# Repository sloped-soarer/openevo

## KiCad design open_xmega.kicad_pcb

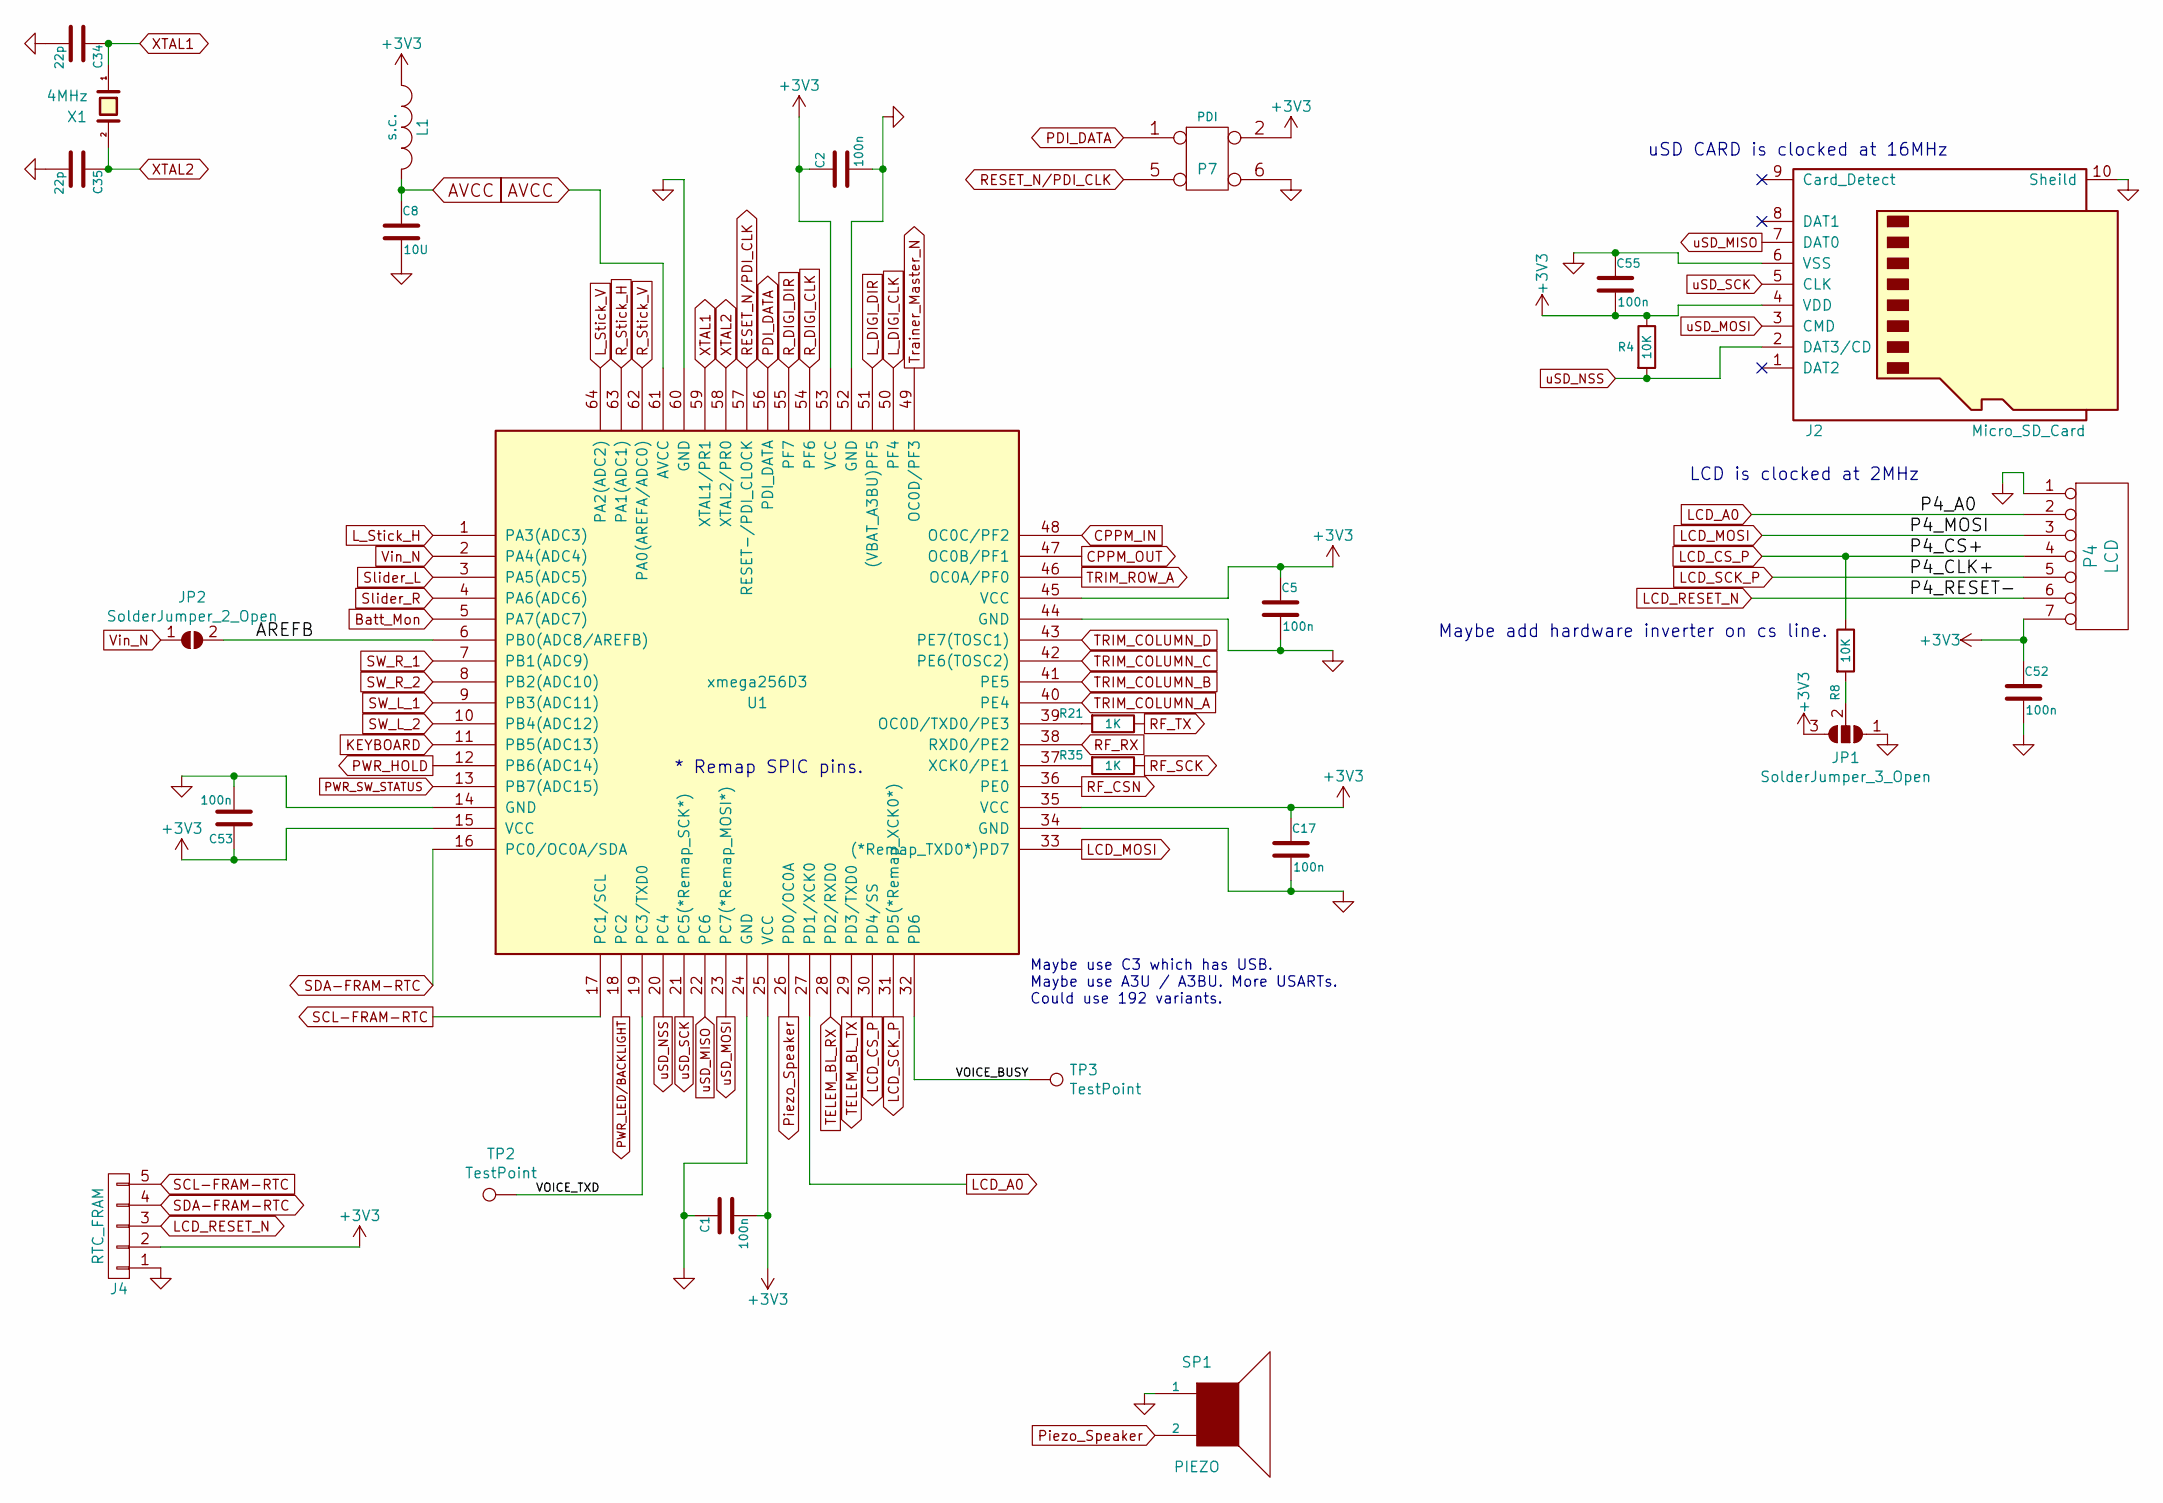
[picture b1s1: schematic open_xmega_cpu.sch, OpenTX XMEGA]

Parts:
C1, C2, C5, C17, C52, C53, C55: 100n; SM0805
C8: 10U; SM1206POL
C34, C35: 22p; SM0805
J2: Micro_SD_Card; HRS_uSD_DM3CS
J4: RTC_FRAM; AVX_00-9159005551X06
JP1: SolderJumper_3_Open; SolderJumper-3_P1.3mm_Open_RoundedPad1.0x1.5mm
JP2: SolderJumper_2_Open; SolderJumper-2_P1.3mm_Open_RoundedPad1.0x1.5mm
L1: s.c.; SM0805
P4: LCD; MOLEX_52808-0770
P7: PDI; PinHeader_2x03_P2.54mm_Vertical_missing_3&4
R4, R8: 10K; SM0805
R21, R35: 1K; SM0805
SP1: PIEZO; Sounder_ABT-436-RC
TP2, TP3: TestPoint; TestPoint_THTPad_1.0x1.0mm_Drill0.5mm
U1: xmega256D3; TQFP64
X1: 4MHz; Crystal_SMD_HC49-SD

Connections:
+3V3: C1.2, C2.1, C5.1, C17.1, C52.1, C53.1, C55.2, J2.4 (VDD), J4.2, JP1.3 (B), L1.1, P4.7, P7.2, R4.1, U1.15 (VCC), U1.25 (VCC), U1.35 (VCC), U1.45 (VCC), U1.53 (VCC); also elsewhere on the board
/open_xmega_cpu/AREFB: JP2.2 (B), U1.6 (PB0(ADC8/AREFB))
/open_xmega_cpu/VOICE_BUSY: TP3.1, U1.32 (PD6)
/open_xmega_cpu/VOICE_TXD: TP2.1, U1.19 (PC3/TXD0)
AVCC: C8.1, L1.2, U1.61 (AVCC)
Batt_Mon: U1.5 (PA7(ADC7)); also elsewhere on the board
CPPM_IN: U1.48 (OC0C/PF2); also elsewhere on the board
CPPM_OUT: U1.47 (OC0B/PF1); also elsewhere on the board
GND: C1.1, C2.2, C5.2, C8.2, C17.2, C34.2, C35.2, C52.2, C53.2, C55.1, J2.6 (VSS), J2.10 (Sheild), J4.1, JP1.1 (A), P4.1, P7.6, SP1.1, U1.14 (GND), U1.24 (GND), U1.34 (GND), U1.44 (GND), U1.52 (GND), U1.60 (GND); also elsewhere on the board
KEYBOARD: U1.11 (PB5(ADC13)); also elsewhere on the board
LCD_A0: P4.2, U1.27 (PD1/XCK0)
LCD_CS_P: P4.4, R8.1, U1.30 (PD4/SS)
LCD_MOSI: P4.3, U1.33 ((*Remap_TXD0*)PD7)
LCD_RESET_N: J4.3, P4.6
LCD_SCK_P: P4.5, U1.31 (PD5(*Remap_XCK0*))
L_DIGI_CLK: U1.50 (PF4); also elsewhere on the board
L_DIGI_DIR: U1.51 ((VBAT_A3BU)PF5); also elsewhere on the board
L_Stick_H: U1.1 (PA3(ADC3)); also elsewhere on the board
L_Stick_V: U1.64 (PA2(ADC2)); also elsewhere on the board
unnamed: JP1.2 (C), R8.2
unnamed: R21.2, U1.39 (OC0D/TXD0/PE3)
unnamed: R35.2, U1.37 (XCK0/PE1)
PDI_DATA: P7.1, U1.56 (PDI_DATA)
PWR_HOLD: U1.12 (PB6(ADC14)); also elsewhere on the board
PWR_LED/BACKLIGHT: U1.18 (PC2); also elsewhere on the board
PWR_SW_STATUS: U1.13 (PB7(ADC15)); also elsewhere on the board
Piezo_Speaker: SP1.2, U1.26 (PD0/OC0A)
RESET_N/PDI_CLK: P7.5, U1.57 (RESET-/PDI_CLOCK); also elsewhere on the board
RF_CSN: U1.36 (PE0); also elsewhere on the board
RF_RX: U1.38 (RXD0/PE2); also elsewhere on the board
RF_SCK: R35.1; also elsewhere on the board
RF_TX: R21.1; also elsewhere on the board
R_DIGI_CLK: U1.54 (PF6); also elsewhere on the board
R_DIGI_DIR: U1.55 (PF7); also elsewhere on the board
R_Stick_H: U1.63 (PA1(ADC1)); also elsewhere on the board
R_Stick_V: U1.62 (PA0(AREFA/ADC0)); also elsewhere on the board
SCL-FRAM-RTC: J4.5, U1.17 (PC1/SCL)
SDA-FRAM-RTC: J4.4, U1.16 (PC0/OC0A/SDA)
SW_L_1: U1.9 (PB3(ADC11)); also elsewhere on the board
SW_L_2: U1.10 (PB4(ADC12)); also elsewhere on the board
SW_R_1: U1.7 (PB1(ADC9)); also elsewhere on the board
SW_R_2: U1.8 (PB2(ADC10)); also elsewhere on the board
Slider_L: U1.3 (PA5(ADC5)); also elsewhere on the board
Slider_R: U1.4 (PA6(ADC6)); also elsewhere on the board
TELEM_BL_RX: U1.28 (PD2/RXD0); also elsewhere on the board
TELEM_BL_TX: U1.29 (PD3/TXD0); also elsewhere on the board
TRIM_COLUMN_A: U1.40 (PE4); also elsewhere on the board
TRIM_COLUMN_B: U1.41 (PE5); also elsewhere on the board
TRIM_COLUMN_C: U1.42 (PE6(TOSC2)); also elsewhere on the board
TRIM_COLUMN_D: U1.43 (PE7(TOSC1)); also elsewhere on the board
TRIM_ROW_A: U1.46 (OC0A/PF0); also elsewhere on the board
Trainer_Master_N: U1.49 (OC0D/PF3); also elsewhere on the board
Vin_N: JP2.1 (A), U1.2 (PA4(ADC4)); also elsewhere on the board
XTAL1: C34.1, U1.59 (XTAL1/PR1), X1.1 (a)
XTAL2: C35.1, U1.58 (XTAL2/PR0), X1.2 (b)
uSD_MISO: J2.7 (DAT0), U1.22 (PC6)
uSD_MOSI: J2.3 (CMD), U1.23 (PC7(*Remap_MOSI*))
uSD_NSS: J2.2 (DAT3/CD), R4.2, U1.20 (PC4)
uSD_SCK: J2.5 (CLK), U1.21 (PC5(*Remap_SCK*))

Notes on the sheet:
LCD is clocked at 2MHz
* Remap SPIC pins.
uSD CARD is clocked at 16MHz
Maybe use C3 which has USB. Maybe use A3U / A3BU. More USARTs. Could use 192 variants.
Maybe add hardware inverter on cs line.

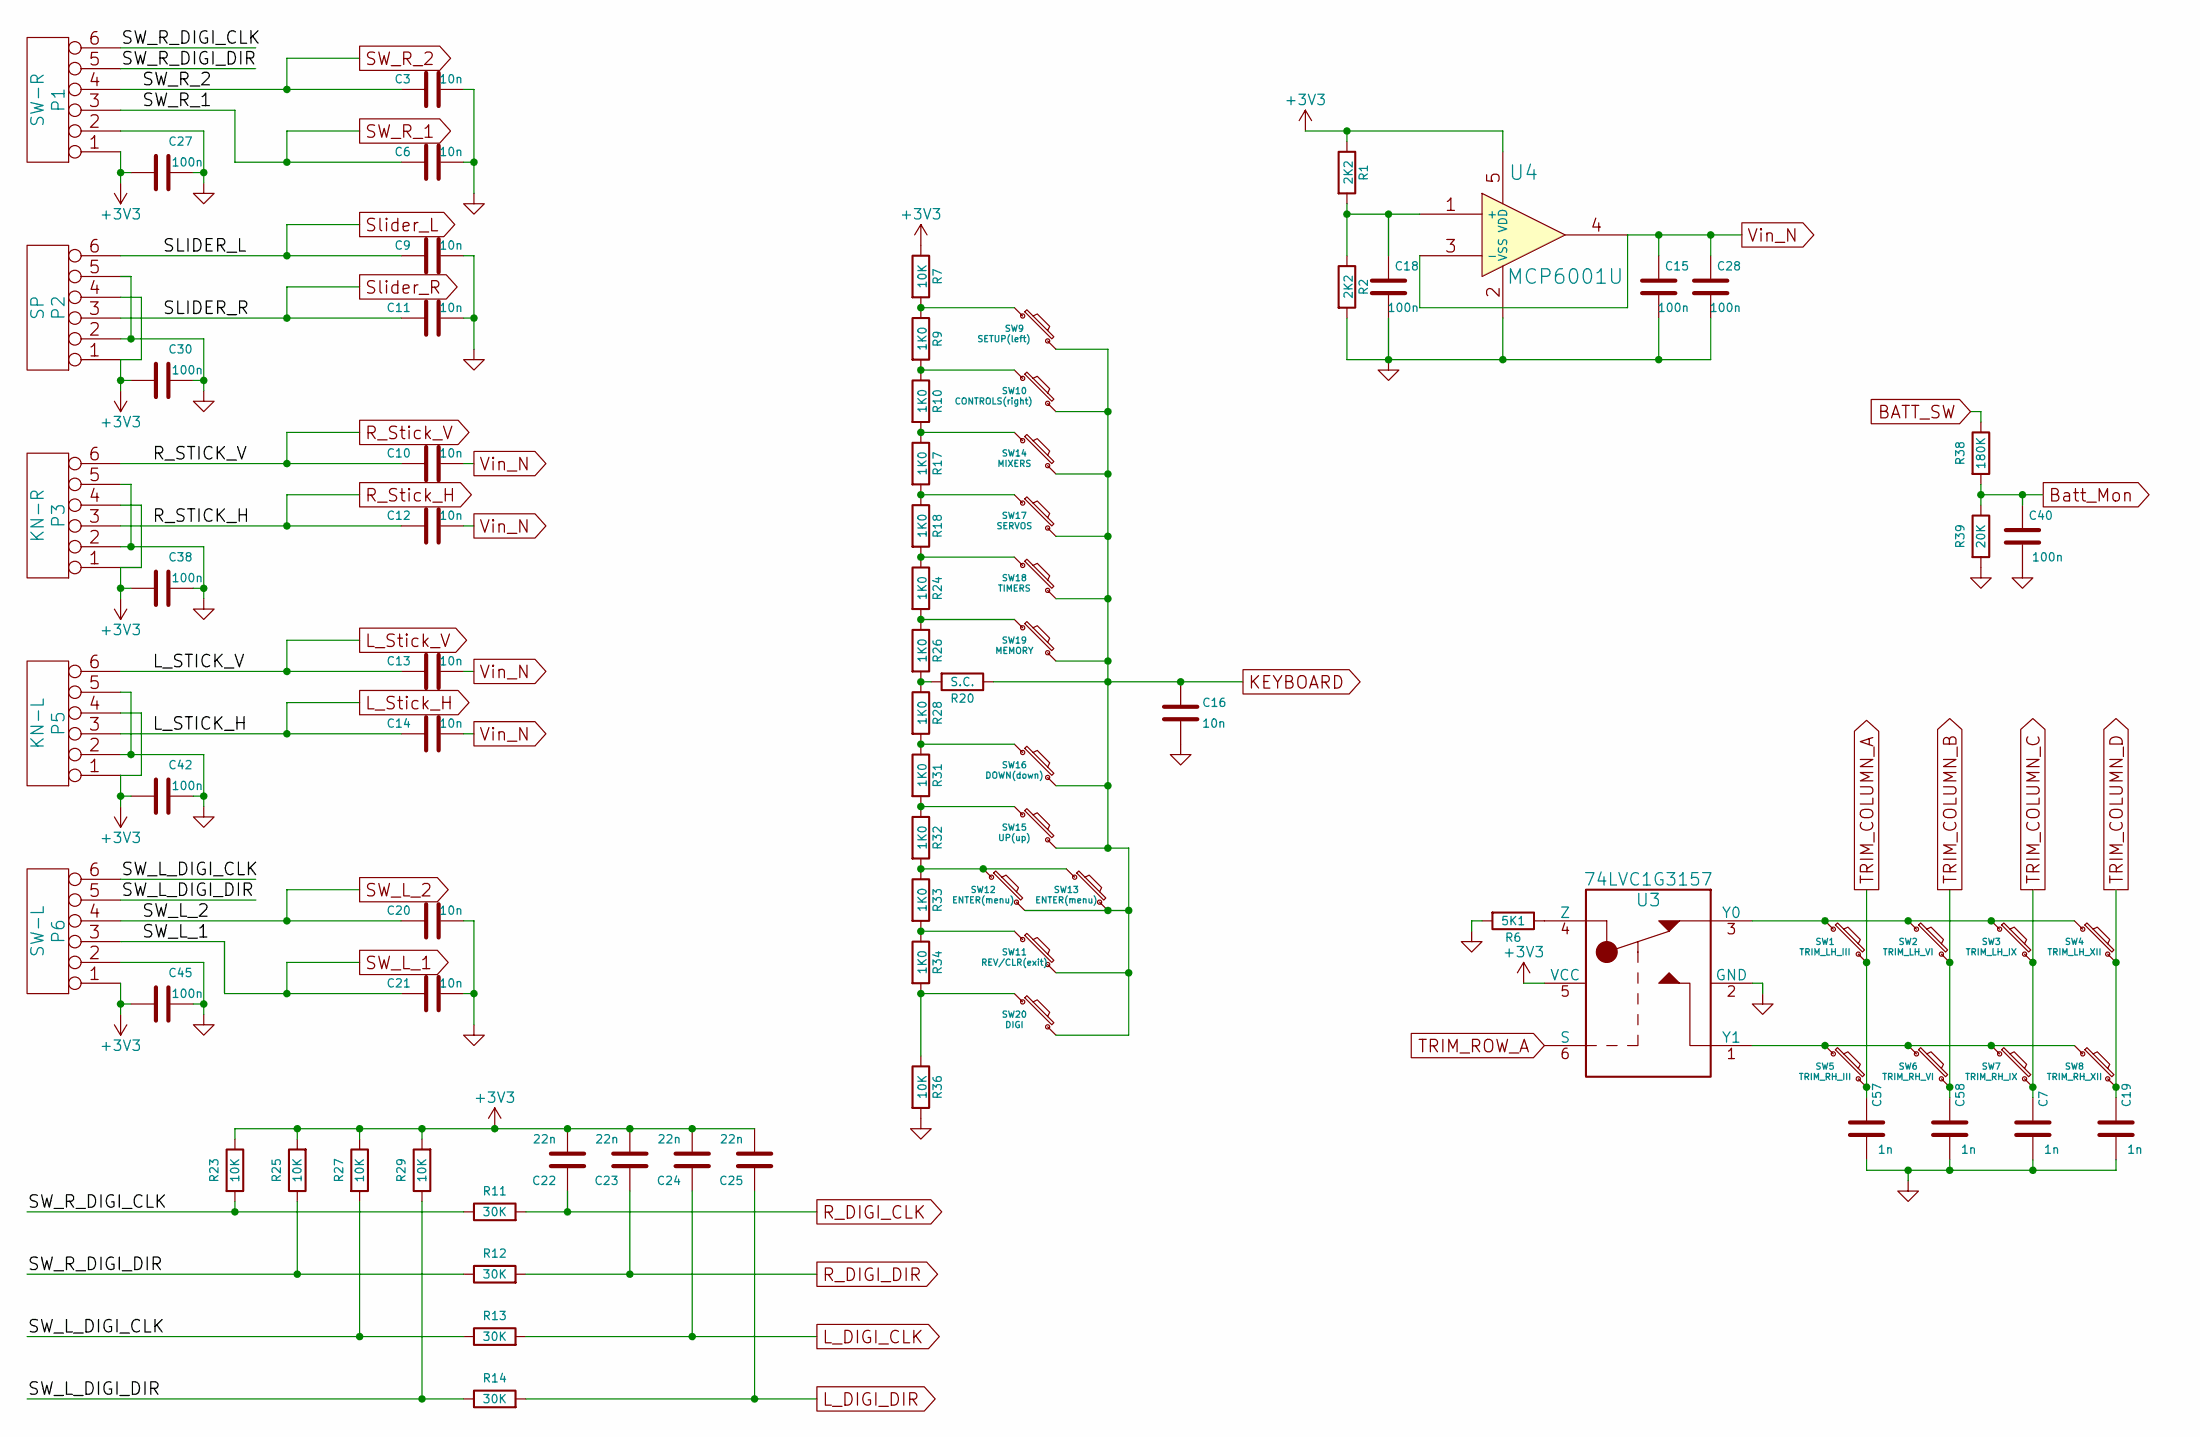
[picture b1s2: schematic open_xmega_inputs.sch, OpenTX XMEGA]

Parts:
C3, C6, C9, C10, C11, C12, C13, C14, C16, C20, C21: 10n; SM0805
C7, C19, C57, C58: 1n; SM0805
C15, C18, C27, C28, C30, C38, C40, C42, C45: 100n; SM0805
C22, C23, C24, C25: 22n; SM0805
P1: SW-R; JST_B6B-ZR-3.4
P2: SP; JST_B6B-ZR-3.4
P3: KN-R; JST_B6B-ZR-3.4
P5: KN-L; JST_B6B-ZR-3.4
P6: SW-L; JST_B6B-ZR-3.4
R1, R2: 2K2; SM0805
R6: 5K1; SM0805
R7, R23, R25, R27, R29, R36: 10K; SM0805
R9, R10, R17, R18, R24, R26, R28, R31, R32, R33, R34: 1K0; SM0805
R11, R12, R13, R14: 30K; SM0805
R20: S.C.; SM0805
R38: 180K; SM0805
R39: 20K; SM0805
SW1: TRIM_LH_III; sw_tact_6x6_smd
SW2: TRIM_LH_VI; sw_tact_6x6_smd
SW3: TRIM_LH_IX; sw_tact_6x6_smd
SW4: TRIM_LH_XII; sw_tact_6x6_smd
SW5: TRIM_RH_III; sw_tact_6x6_smd
SW6: TRIM_RH_VI; sw_tact_6x6_smd
SW7: TRIM_RH_IX; sw_tact_6x6_smd
SW8: TRIM_RH_XII; sw_tact_6x6_smd
SW9: SETUP(left); sw_tact_6x6_smd
SW10: CONTROLS(right); sw_tact_6x6_smd
SW11: REV/CLR(exit); sw_tact_6x6_smd
SW12, SW13: ENTER(menu); sw_tact_6x6_smd
SW14: MIXERS; sw_tact_6x6_smd
SW15: UP(up); sw_tact_6x6_smd
SW16: DOWN(down); sw_tact_6x6_smd
SW17: SERVOS; sw_tact_6x6_smd
SW18: TIMERS; sw_tact_6x6_smd
SW19: MEMORY; sw_tact_6x6_smd
SW20: DIGI; sw_tact_6x6_smd
U3: 74LVC1G3157; SOT-23-6
U4: MCP6001U; SOT-23-5

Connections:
+3V3: C22.2, C23.2, C24.2, C25.2, C27.1, C30.1, C38.1, C42.1, C45.1, P1.1, P2.1, P2.4, P3.1, P3.4, P5.1, P5.4, P6.1, R1.1, R7.1, R23.1, R25.2, R27.1, R29.2, U3.5 (VCC), U4.5 (VDD); also elsewhere on the board
/open_xmega_inputs/SW_L_DIGI_CLK: P6.6, R13.1, R27.2
/open_xmega_inputs/SW_L_DIGI_DIR: P6.5, R14.1, R29.1
/open_xmega_inputs/SW_R_DIGI_CLK: P1.6, R11.1, R23.2
/open_xmega_inputs/SW_R_DIGI_DIR: P1.5, R12.1, R25.1
BATT_SW: R38.1; also elsewhere on the board
Batt_Mon: C40.2, R38.2, R39.1; also elsewhere on the board
GND: C3.2, C6.2, C7.2, C9.2, C11.2, C15.1, C16.2, C18.1, C19.2, C20.2, C21.2, C27.2, C28.1, C30.2, C38.2, C40.1, C42.2, C45.2, C57.2, C58.2, P1.2, P2.2, P2.5, P3.2, P3.5, P5.2, P5.5, P6.2, R2.2, R6.2, R36.2, R39.2, U3.2 (GND), U4.2 (VSS); also elsewhere on the board
KEYBOARD: C16.1, R20.1, SW9.2, SW10.2, SW11.2, SW12.2, SW13.2, SW14.2, SW15.2, SW16.2, SW17.2, SW18.2, SW19.2, SW20.2; also elsewhere on the board
L_DIGI_CLK: C24.1, R13.2; also elsewhere on the board
L_DIGI_DIR: C25.1, R14.2; also elsewhere on the board
L_Stick_H: C14.1, P5.3; also elsewhere on the board
L_Stick_V: C13.1, P5.6; also elsewhere on the board
unnamed: C18.2, R1.2, R2.1, U4.1 (+)
unnamed: R6.1, U3.4 (Z)
unnamed: R7.2, R9.1, SW9.1
unnamed: R9.2, R10.1, SW10.1
unnamed: R10.2, R17.1, SW14.1
unnamed: R17.2, R18.1, SW17.1
unnamed: R18.2, R24.1, SW18.1
unnamed: R20.2, R26.2, R28.1
unnamed: R24.2, R26.1, SW19.1
unnamed: R28.2, R31.1, SW16.1
unnamed: R31.2, R32.1, SW15.1
unnamed: R32.2, R33.1, SW12.1, SW13.1
unnamed: R33.2, R34.1, SW11.1
unnamed: R34.2, R36.1, SW20.1
unnamed: SW1.1, SW2.1, SW3.1, SW4.1, U3.3 (Y0)
unnamed: SW5.1, SW6.1, SW7.1, SW8.1, U3.1 (Y1)
R_DIGI_CLK: C22.1, R11.2; also elsewhere on the board
R_DIGI_DIR: C23.1, R12.2; also elsewhere on the board
R_Stick_H: C12.1, P3.3; also elsewhere on the board
R_Stick_V: C10.1, P3.6; also elsewhere on the board
SW_L_1: C21.1, P6.3; also elsewhere on the board
SW_L_2: C20.1, P6.4; also elsewhere on the board
SW_R_1: C6.1, P1.3; also elsewhere on the board
SW_R_2: C3.1, P1.4; also elsewhere on the board
Slider_L: C9.1, P2.6; also elsewhere on the board
Slider_R: C11.1, P2.3; also elsewhere on the board
TRIM_COLUMN_A: C57.1, SW1.2, SW5.2; also elsewhere on the board
TRIM_COLUMN_B: C58.1, SW2.2, SW6.2; also elsewhere on the board
TRIM_COLUMN_C: C7.1, SW3.2, SW7.2; also elsewhere on the board
TRIM_COLUMN_D: C19.1, SW4.2, SW8.2; also elsewhere on the board
TRIM_ROW_A: U3.6 (S); also elsewhere on the board
Vin_N: C10.2, C12.2, C13.2, C14.2, C15.2, C28.2, U4.3 (-), U4.4; also elsewhere on the board

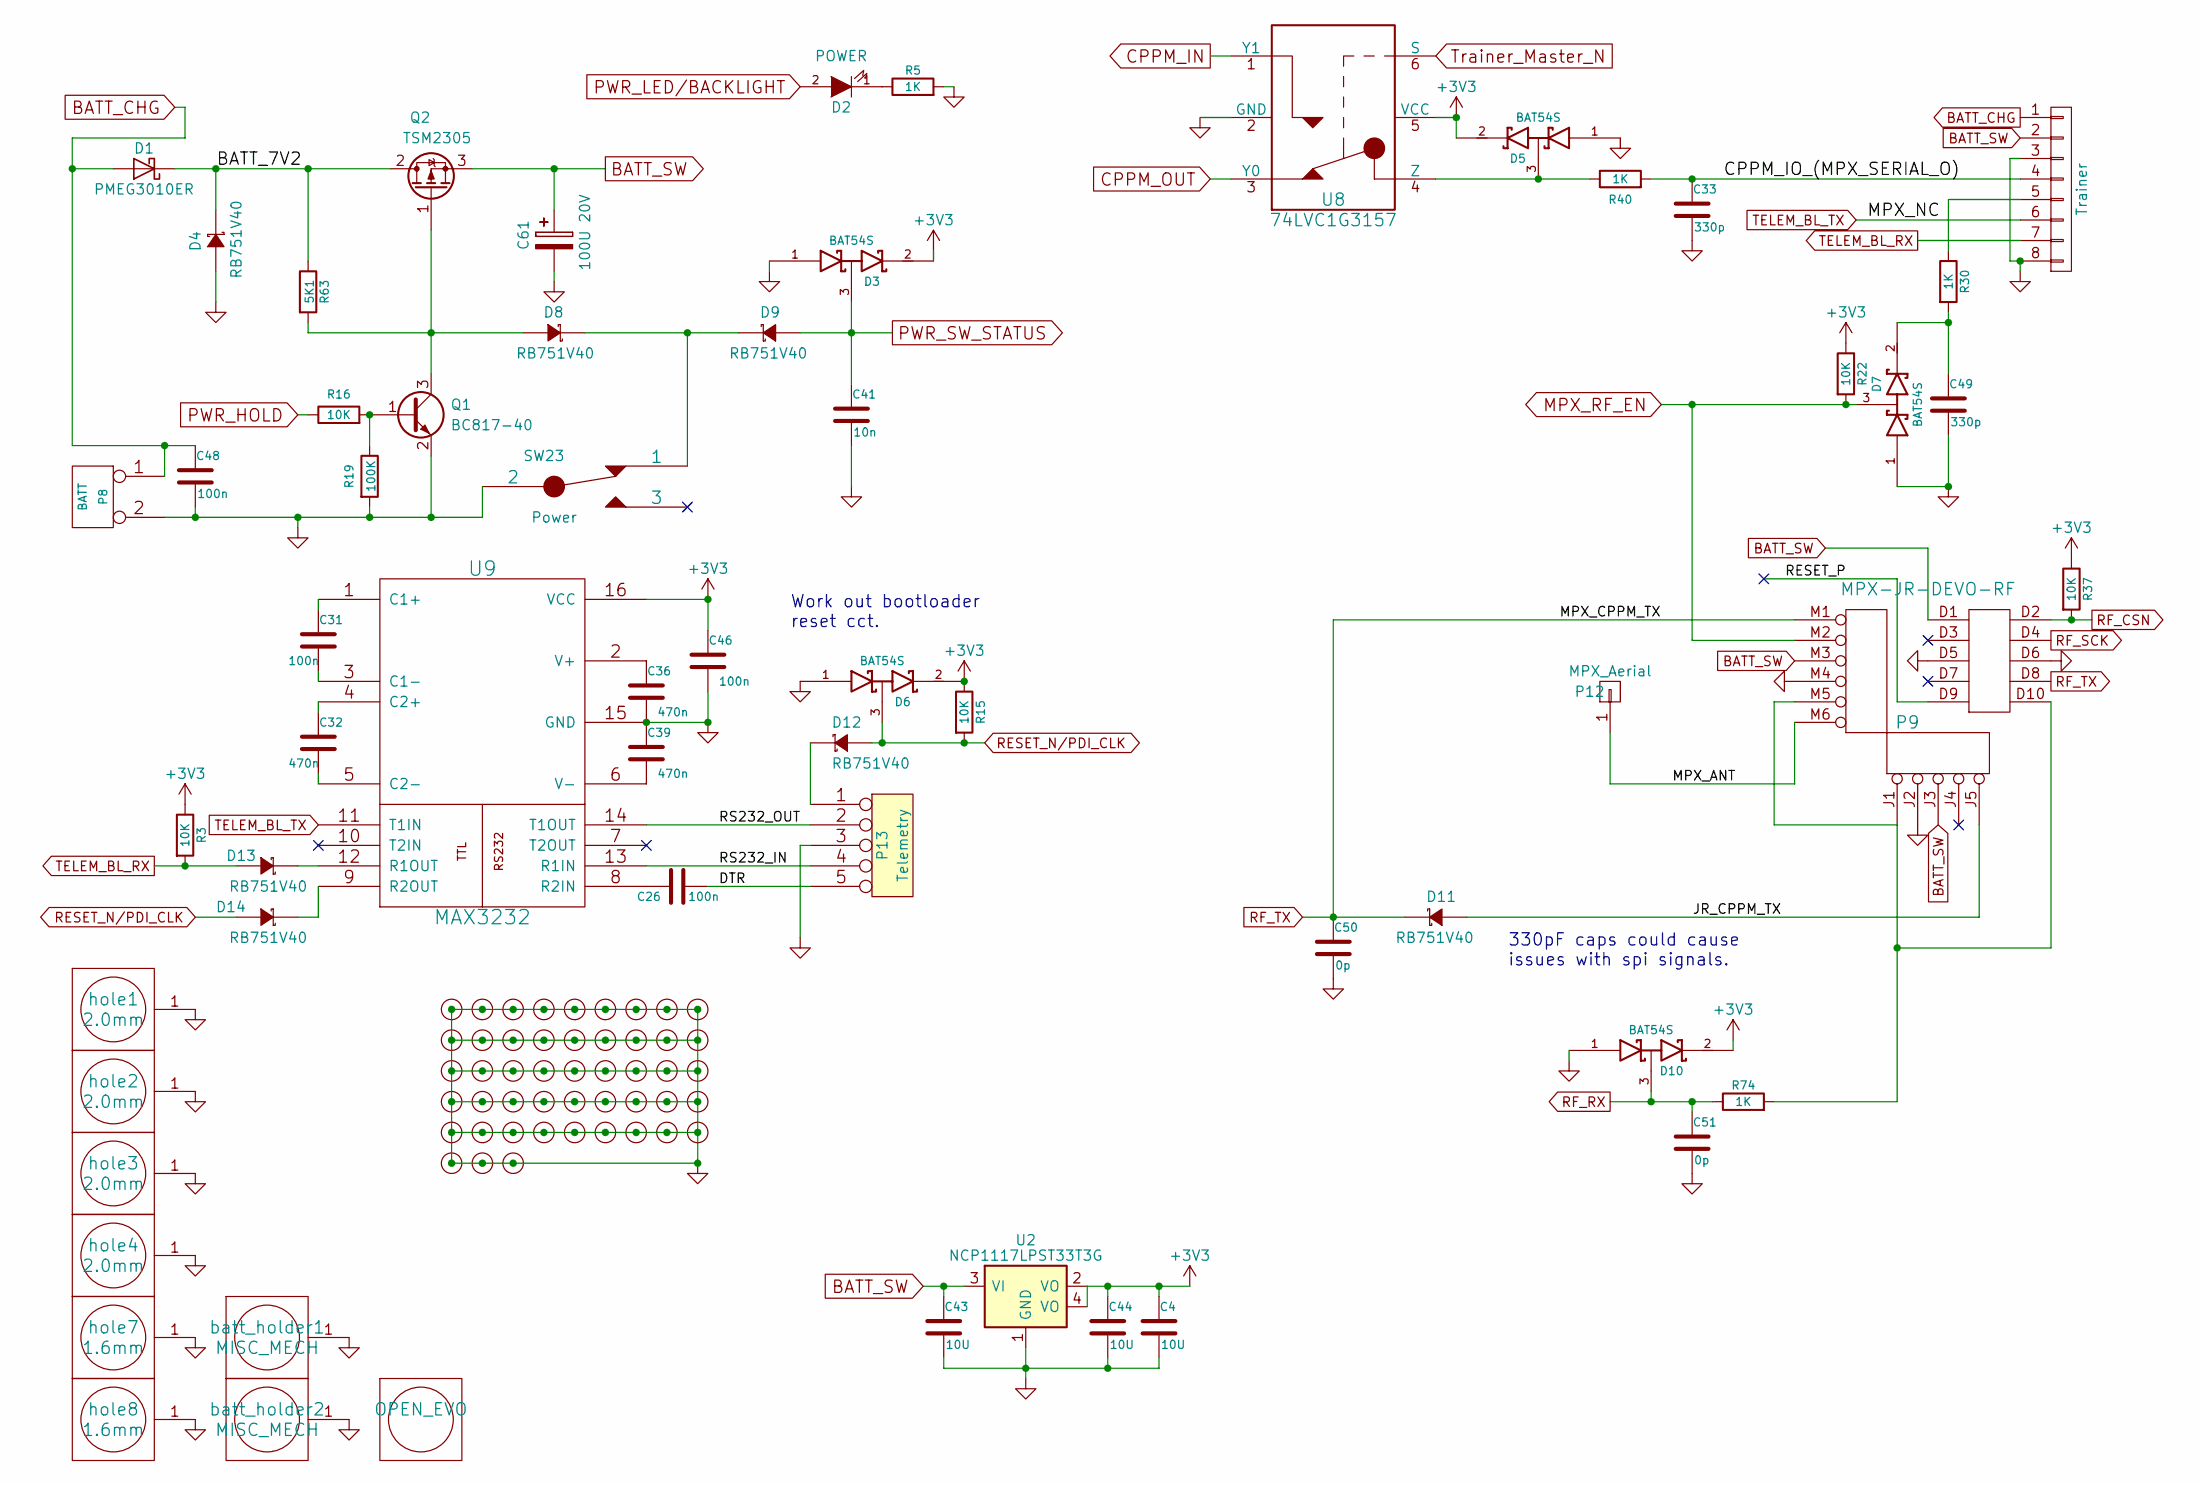
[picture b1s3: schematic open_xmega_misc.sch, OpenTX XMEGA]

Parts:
C4, C43, C44: 10U; SM1206POL
C26, C31, C46, C48: 100n; SM0805
C32, C36, C39: 470n; SM0805
C33, C49: 330p; SM0805
C41: 10n; SM0805
C50, C51: 0p; SM0805
C61: 100U 20V; CP_Elec_6.3x7.7
D1: PMEG3010ER; SOD-123W
D2: POWER; LED_D5.0mm_FlatTop
D3, D5, D6, D7, D10: BAT54S; SOT-23
D4, D8, D9, D11, D12, D13, D14: RB751V40; SOD-323
Logo1: OPEN_EVO; OPEN_EVO_logo
P8: BATT; Lumberg_732782
P9: MPX-JR-DEVO-RF; RF_MODULE
P10: Trainer; Generic_DIN_7_hirschmann-cui
P12: MPX_Aerial; aerial_tag
P13: Telemetry; PinHeader_1x05_P2.54mm_Vertical
Q1: BC817-40; SOT-23
Q2: TSM2305; SOT-23
R3, R15, R16, R22, R37: 10K; SM0805
R5, R30, R40, R74: 1K; SM0805
R19: 100K; SM0805
R63: 5K1; SM0805
SW23: Power; SW_COMAX6_SPDT
U2: NCP1117LPST33T3G; SOT-223
U8: 74LVC1G3157; SOT-23-6
U9: MAX3232; SOIC-16
batt_holder1, batt_holder2: MISC_MECH; evo_battery_holder
hole1, hole2, hole3, hole4: 2.0mm; hole_2-0mm
hole7, hole8: 1.6mm; hole_1-6mm
v1, v2, v3, v4, v5, v6, v7, v8, v9, v10, v11, v12, v13, v14, v15, v16, v17, v18, v19, v20, v21, v22, v23, v24, v25, v26, v27, v28, v29, v30, v31, v32, v33, v34, v35, v36, v37, v38, v39, v40, v41, v42, v43, v44, v45, v46, v47, v48: gnd_via; GND_PLANE_VIA

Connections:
+3V3: C4.1, C44.1, C46.1, D3.2 (K), D5.2 (K), D6.2 (K), D10.2 (K), R3.1, R15.1, R22.1, R37.1, U2.2 (VO), U2.4 (VO), U8.5 (VCC), U9.16 (VCC); also elsewhere on the board
/open_xmega_misc/BATT_7V2: D1.1 (K), D4.1 (K), Q2.2 (D), R63.1
/open_xmega_misc/CPPM_IO_(MPX_SERIAL_O): C33.1, P10.4, R40.2
/open_xmega_misc/DTR: C26.1, P13.5
/open_xmega_misc/JR_CPPM_TX: D11.2 (A), P9.J5 (JR_CPPM)
/open_xmega_misc/MPX_ANT: P9.M6 (MPX_ANT), P12.1
/open_xmega_misc/RESET_P: P9.D9 (RESET_P)
/open_xmega_misc/RS232_IN: P13.4, U9.13 (R1IN)
/open_xmega_misc/RS232_OUT: P13.2, U9.14 (T1OUT)
BATT_CHG: C48.1, D1.2 (A), P8.1, P10.1
BATT_SW: C43.1, C61.1, P9.D1 (+5V), P9.J3 (JR_PWR), P9.M3 (MPX_PWR), P10.2, Q2.3 (S), U2.3 (VI); also elsewhere on the board
CPPM_IN: U8.1 (Y1); also elsewhere on the board
CPPM_OUT: U8.3 (Y0); also elsewhere on the board
GND: C4.2, C33.2, C36.2, C39.1, C41.2, C43.2, C44.2, C46.2, C48.2, C49.2, C50.2, C51.2, C61.2, D3.1 (A), D4.2 (A), D5.1 (A), D6.1 (A), D7.1 (A), D10.1 (A), P8.2 (PM), P9.D5 (GND), P9.D6 (GND), P9.J2 (JR_GND), P9.M4 (MPX_GND), P10.3, P10.8, P13.3, Q1.2 (E), R5.2, R19.2, SW23.2, U2.1 (GND), U8.2 (GND), U9.15 (GND), batt_holder1.1, batt_holder2.1, hole1.1, hole2.1, hole3.1, hole4.1, hole7.1, hole8.1, v1.1, v2.1, v3.1, v4.1, v5.1, v6.1, v7.1, v8.1, v9.1, v10.1, v11.1, v12.1, v13.1, v14.1, v15.1, v16.1, v17.1, v18.1, v19.1, v20.1, v21.1, v22.1, v23.1, v24.1, v25.1, v26.1, v27.1, v28.1, v29.1, v30.1, v31.1, v32.1, v33.1, v34.1, v35.1, v36.1, v37.1, v38.1, v39.1, v40.1, v41.1, v42.1, v43.1, v44.1, v45.1, v46.1, v47.1, v48.1; also elsewhere on the board
MPX_RF_EN: D7.3 (AK), P9.M2 (MPX_RF_EN), R22.2
unnamed: C26.2, U9.8 (R2IN)
unnamed: C31.1, U9.1 (C1+)
unnamed: C31.2, U9.3 (C1-)
unnamed: C32.1, U9.4 (C2+)
unnamed: C32.2, U9.5 (C2-)
unnamed: C36.1, U9.2 (V+)
unnamed: C39.2, U9.6 (V-)
unnamed: C49.1, D7.2 (K), R30.2
unnamed: D2.1 (K), R5.1
unnamed: D5.3 (AK), R40.1, U8.4 (Z)
unnamed: D8.1 (K), D9.1 (K), SW23.1
unnamed: D8.2 (A), Q1.3 (C), Q2.1 (G), R63.2
unnamed: D12.1 (K), P13.1
unnamed: D13.1 (K), U9.12 (R1OUT)
unnamed: D14.1 (K), U9.9 (R2OUT)
unnamed: P9.D10 (MISO), P9.J1 (JR_NC), P9.M5 (MPX_RX), R74.2
unnamed: P10.5, R30.1
unnamed: Q1.1 (B), R16.2, R19.1
PWR_HOLD: R16.1; also elsewhere on the board
PWR_LED/BACKLIGHT: D2.2 (A); also elsewhere on the board
PWR_SW_STATUS: C41.1, D3.3 (AK), D9.2 (A); also elsewhere on the board
RESET_N/PDI_CLK: D6.3 (AK), D12.2 (A), D14.2 (A), R15.2; also elsewhere on the board
RF_CSN: P9.D2 (CS), R37.2; also elsewhere on the board
RF_RX: C51.1, D10.3 (AK), R74.1; also elsewhere on the board
RF_SCK: P9.D4 (SCK); also elsewhere on the board
RF_TX: C50.1, D11.1 (K), P9.D8 (MOSI), P9.M1 (MPX_TX_CPPM); also elsewhere on the board
TELEM_BL_RX: D13.2 (A), P10.7, R3.2; also elsewhere on the board
TELEM_BL_TX: P10.6, U9.11 (T1IN); also elsewhere on the board
Trainer_Master_N: U8.6 (S); also elsewhere on the board

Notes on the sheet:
330pF caps could cause issues with spi signals.
Work out bootloader reset cct.

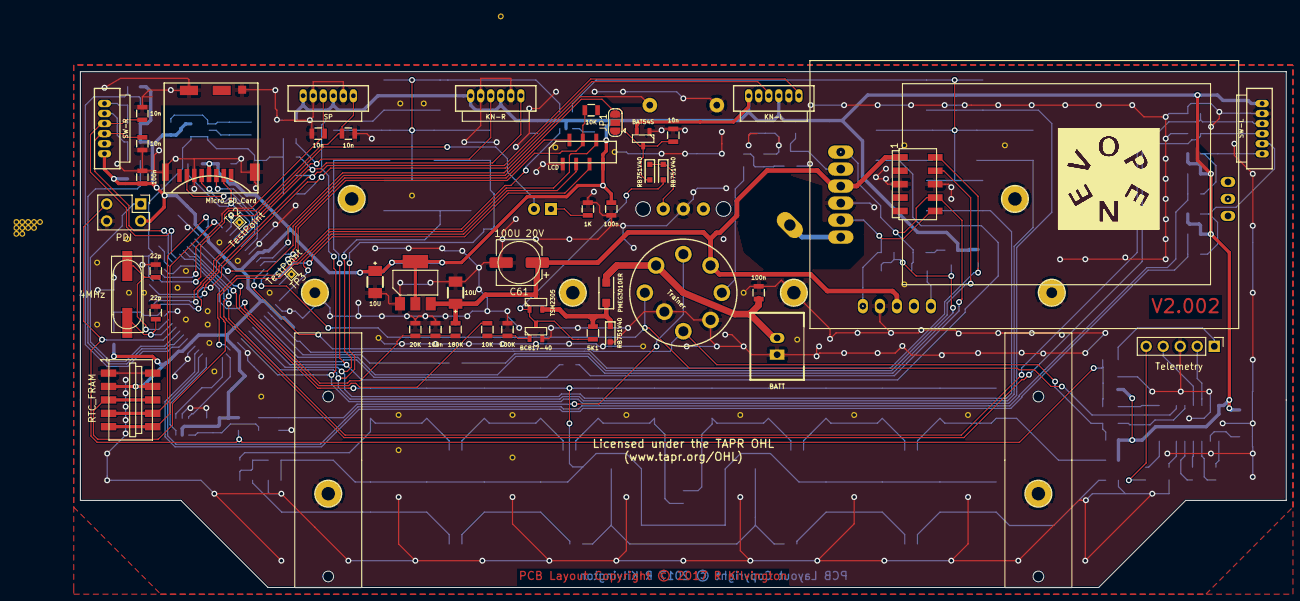
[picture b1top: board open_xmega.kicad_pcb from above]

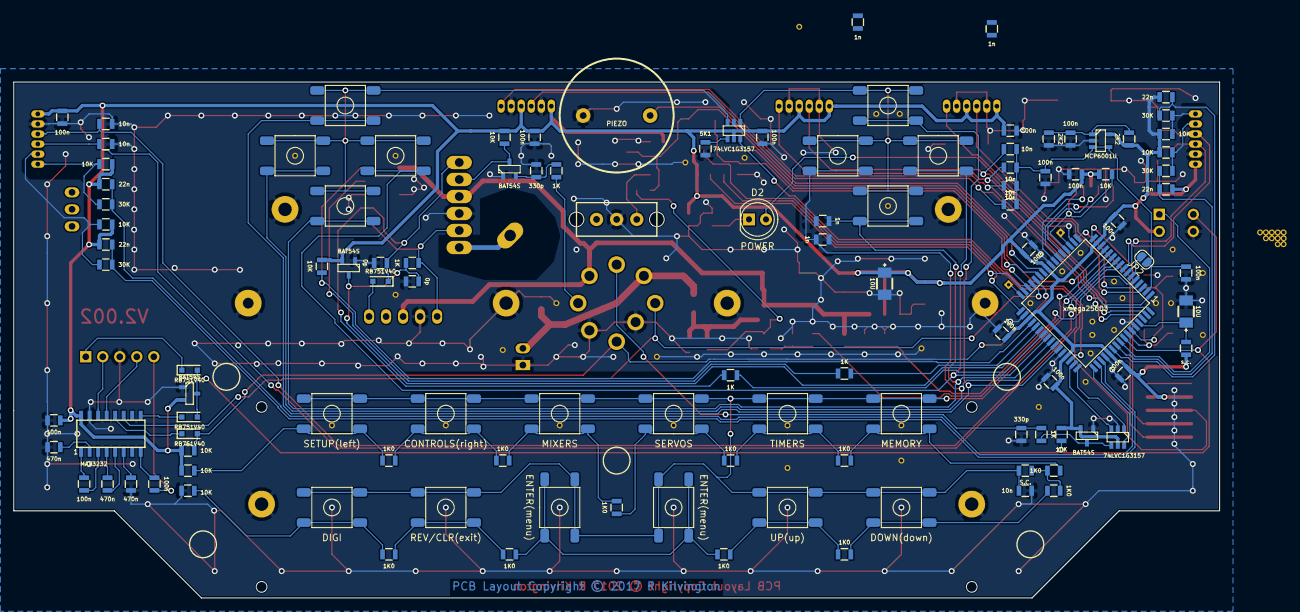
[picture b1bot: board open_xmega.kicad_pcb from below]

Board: 2 copper layers, 180.0 x 77.0 mm, 217 parts (113 on the bottom side), 107 nets.

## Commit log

2019-05-11 All major track now routed.

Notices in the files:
open_xmega.kicad_pcb:
Copyright © 2017 R Kilvington (eclrpk @ leeds.ac.uk)
Licensed under the TAPR OHL
PCB Layout Copyright © 2017 R Kilvington
open_xmega_cpu.sch:
Copyright © 2017 R Kilvington (kilvi2013 @ gmail.com)
